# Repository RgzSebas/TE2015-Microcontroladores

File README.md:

# **TE2015 Microcontroladores**

This repository aims to help you understand the topics covered in TE2015 Microcontroladores. Particulary, we will address the following:
* To understand the architecture of a PIC18 microcontroller
* To become familiar with PIC18 instruction set to develop firmware
* To carry out coding, programming and debugging of PIC18 firmware using MPLAB X IDE
* To interface a microcontroller with an external memory or peripheral using both, physical connections and driver develpment 
* To analyze the internal structure of a general purpose input/output port of the microcontroller
* To learn by doing on the develpment of timing-based firmware 
* To study serial communication protocols to communicate a microcontroller with an external device

## Laboratory
| WEEK | DATE | LABORATORY |
| :---: | :--- | :--- |
| 32 |  8 Aug | [LB1 Hardware design: schematic capture](laboratory/LB1/README.md) |
| 33, 34 | 15, 22 Aug | [LB2 Hardware design: physicial layout](laboratory/LB2/README.md) |
| 35 | 29 Aug | [LB3 PIC18 and MPLAB basics](laboratory/LB3/README.md) |
| 36, 37 | 5, 12/Sep  | [LB4 Assembly programming of PIC18](laboratory/LB4/README.md)|
| 38, 39 | 19, 26/Sep | [LB5 Fundamentals of C for PIC programming](laboratory/LB5/README.md) |

<!--
| 41 | 3/Oct  | LB6 GPIO: LCD display |
| 42 | 10/Oct | LB7 GPIO: 4x4 keypad and 7-segment display |
| 43 | 17/Oct | LB8 Hardware interrupts and the Interrupt Service Rutines|
| 44 | 24/Oct | LB8 Hardware interrupts and the Interrupt Service Rutines|
| 45 | 31/Oct | LB9 Timers, comparators and PWM|
| 46 | 7/Nov  | LB10 Analog inputs for microcontrollers|
| 47 | 14/Nov | LB11 Asynchronous serial communications|
| 48 | 21/Nov | HOLIDAY |
-->

## Hands-on Exercises
| NAME | WEEK | TOPIC | DESCRIPTION | LANGUAGE | 
|---|---|---|---|---| 
| [PIC18F4550_BSF.X](mplab/PIC18F4550_BSF.X) | 34 | SFRs | Bank operations using BSR | PIC-AS |
<!--
| [PIC18F57Q43_GPIO_config]| 34 | SFRs & GPIO | Configuration of TRIS y ANSEL SFRs to blink an on-board LED | PIC-AS |
| XXXX | 35 | Stack & Addressing | PENDING | PIC-AS |
| XXXX | 36 | PIC18 ISA | PENDING | PIC-AS |
| XXXX | 37 | Flow control | PENDING | PIC-AS |
| XXXX | 39 | Operators and precedence | PENDING | PIC-AS |
| XXXX | 40 | Flow control | PENDING | C |
| XXXX | 41 | Pointers, Arrays & Scopes| PENDING | C |
| XXXX | 42 | GPIO | PENDING | C |
| XXXX | 44 | Interrupts | PENDING | C |
| XXXX | 45 | Timers | PENDING | C |
| XXXX | 46 | ADC & UART | PENDING | C |
-->

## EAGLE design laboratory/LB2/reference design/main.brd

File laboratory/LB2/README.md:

# LB2. Expansion Board: Physical Layout

## Description
This is the second part of the Expansion Board design. In this part you will finish designing your board by putting all the components' footprints in place inside the board and routing all of the electrical connections along the two sides of the board: top and bottom. Once you are done routing your board, it is important to carry out a test that will let you know if the component placemente and the copper tracks can be fabricated by the manufacturer, which is called the Design Rule Check (DRC). For this, we need to set the manufacturer's design rules first and then perform the test considering such rules you previously established. Once the test is passed, you can be sure the manufacturer is able to fabricate your board without setback. For a better undestanding of the PCB fabrication process, watch the video <a href="https://www.youtube.com/watch?v=YJr-kHy6STg">What is a PCB?</a>.

## Lab Procedure
### __STEP 1. SET THE DESIGN RULES__
After finishing your schematic diagram, the layout view of your board can be created. For this, go to _File_ menu and select _Switch to board_.

Once the board view is open, select _DRC_ under _Tools_ menu to open the design rule window. Across the different tabs of this windows you define the design rules of your design, according to the manufacturer fabrication capabilities. Go through tabs _Clearance_, _Distance_, _Sizes_ and _Annular Ring_ and set the parameters as shown in the figures below. Note that all distances are expressed in __mil__ units, which represents the thousandth of an inch. 

### __STEP 2. PLACE THE COMPONENTS INSIDE THE BOARD BOUNDERIES__
The figure below shows the layout view of your board including all the components and a predefined board with and area of 160 mm x 100 mm. This predifined board is enough to place and route all your components, thus you can start placing the components inside. 

Once you are done placing the components, the board should like as the one shown below. You can readjust the board dimensions if you consider more or less space is suitable for your component arrangement. 

### __STEP 3. ROUTE ALL THE CONNECTIONS__
Route your components by using the Autoroute tool. This way, the tool will make sure that design rules are fulfilled as routing takes place. The routing process will take some time, depending on your computer. To use the Autorouter tool, select _Autorouter_ under _Tools_ menu. 

You can use the predefined settings as shown below and click _Continue_. The following window shows the percentage of tracks that have been routed by the Autorouter. After clicking _Start_, the tool starts the routing process and you can monitor the progress on the same window.

Once the Autorouter has router 100% of the tracks, you can stop the process by clicking _End Job_. If you leave the process longer, it will try to optimize the tracks by reducing the track length the amount of vias that are placed. It is recommended to allow the Autorouter to optimize the design so it is less prone to fabrication errors. The figure below shows when 100% of the tracks have been routed and you can end the process.

The resulting board will show now all the tracks that interconnect the components in your board. Red tracks correspond to tracks on the top copper layer, and blue tracks show those on the bottom copper layer. 

### __STEP 4. CARRY OUT A DESIGN RULE CHECK__
Open the DRC window and click _Check_ to run the test. In case design errors are found, an error window will pop-up describing the errors found. If no errors are detected, anything will pop up and the test is passed.

### __STEP 5. GENERATE THE GERBER FILES__
Under _File_ select _CAM Processor_. On the CAM Processor window, select _Gerber_ on _Output Files_ to see the Gerber file options. The image below shows the settings for the Gerber files. Make sure `Export as ZIP` and `Gerber RS-274X` are selected.

Under the _Gerber_ tab you can see all the different layers on you design, such as top and bottom copper, soldermasks, silkscreens, etc. Clicking on any of the layers will shown a preview of such layer. 

To generate your files click _Process Job_, find a location for your ZIP file and click _Save_.

The files will be then generated and located in the folder of your choice. 

### __STEP 6. SEND OUT YOUR FILES FOR BOARD MANUFACTURE__
Some manufacturers have a quotation system that allow you to upload your GERBER files to then generate an estimated price for your design. Select the minimum quantity of boards that the manufacturer can fabricate and get an approximate cost for your design. See below three reliable manufacturers with an self quotation system that you can use for your  board:

<p align="center">

</p>

### __STEP 7. GET THE ELECTRONIC COMPONENTS__
The final step is to get the electronic components for your board. In this sense, there is a pre-made Bill of Materials (BOM) that keeps an updated list of components required for the assembly. It is kept on Digikey and you can access it following the link below:
<p align="center">
</p>

The BOM keeps the minimum amount of each component required to assembly one board. Feel free to modify the component quantity in case you want to assemble more than one board or get spares in case you loose or damage any component during assembly and soldering.

If you would like to receive your components at campus instead of a personal address, ask your professor for address details. 

### __DELIVERABLES__
Deliverables for LB2 are:
1. EAGLE project 
   * Include the schematic diagram without ERC errors.
   * PCB layout without DRC errors  
   * Push your project files into your GitHub repository.
2. Demostrative video 
   * Make a 2-minutes video showing the finished board to complement your last video presentation. In this case, perform a DRC test to demonstrate that your design is ready for fabrication.
   * Also, explain the process to generate the Gerber files and show the quotation you get from the manufacturer of your choice.
      
      _Note that a similar DRC will be carried out by the manufacturer to make sure your board can be manufactured. You will get a confirmation if your design is ready for fabrication_. 
   * _Optional:_ Show the 3D view of your video on Fusion 360.

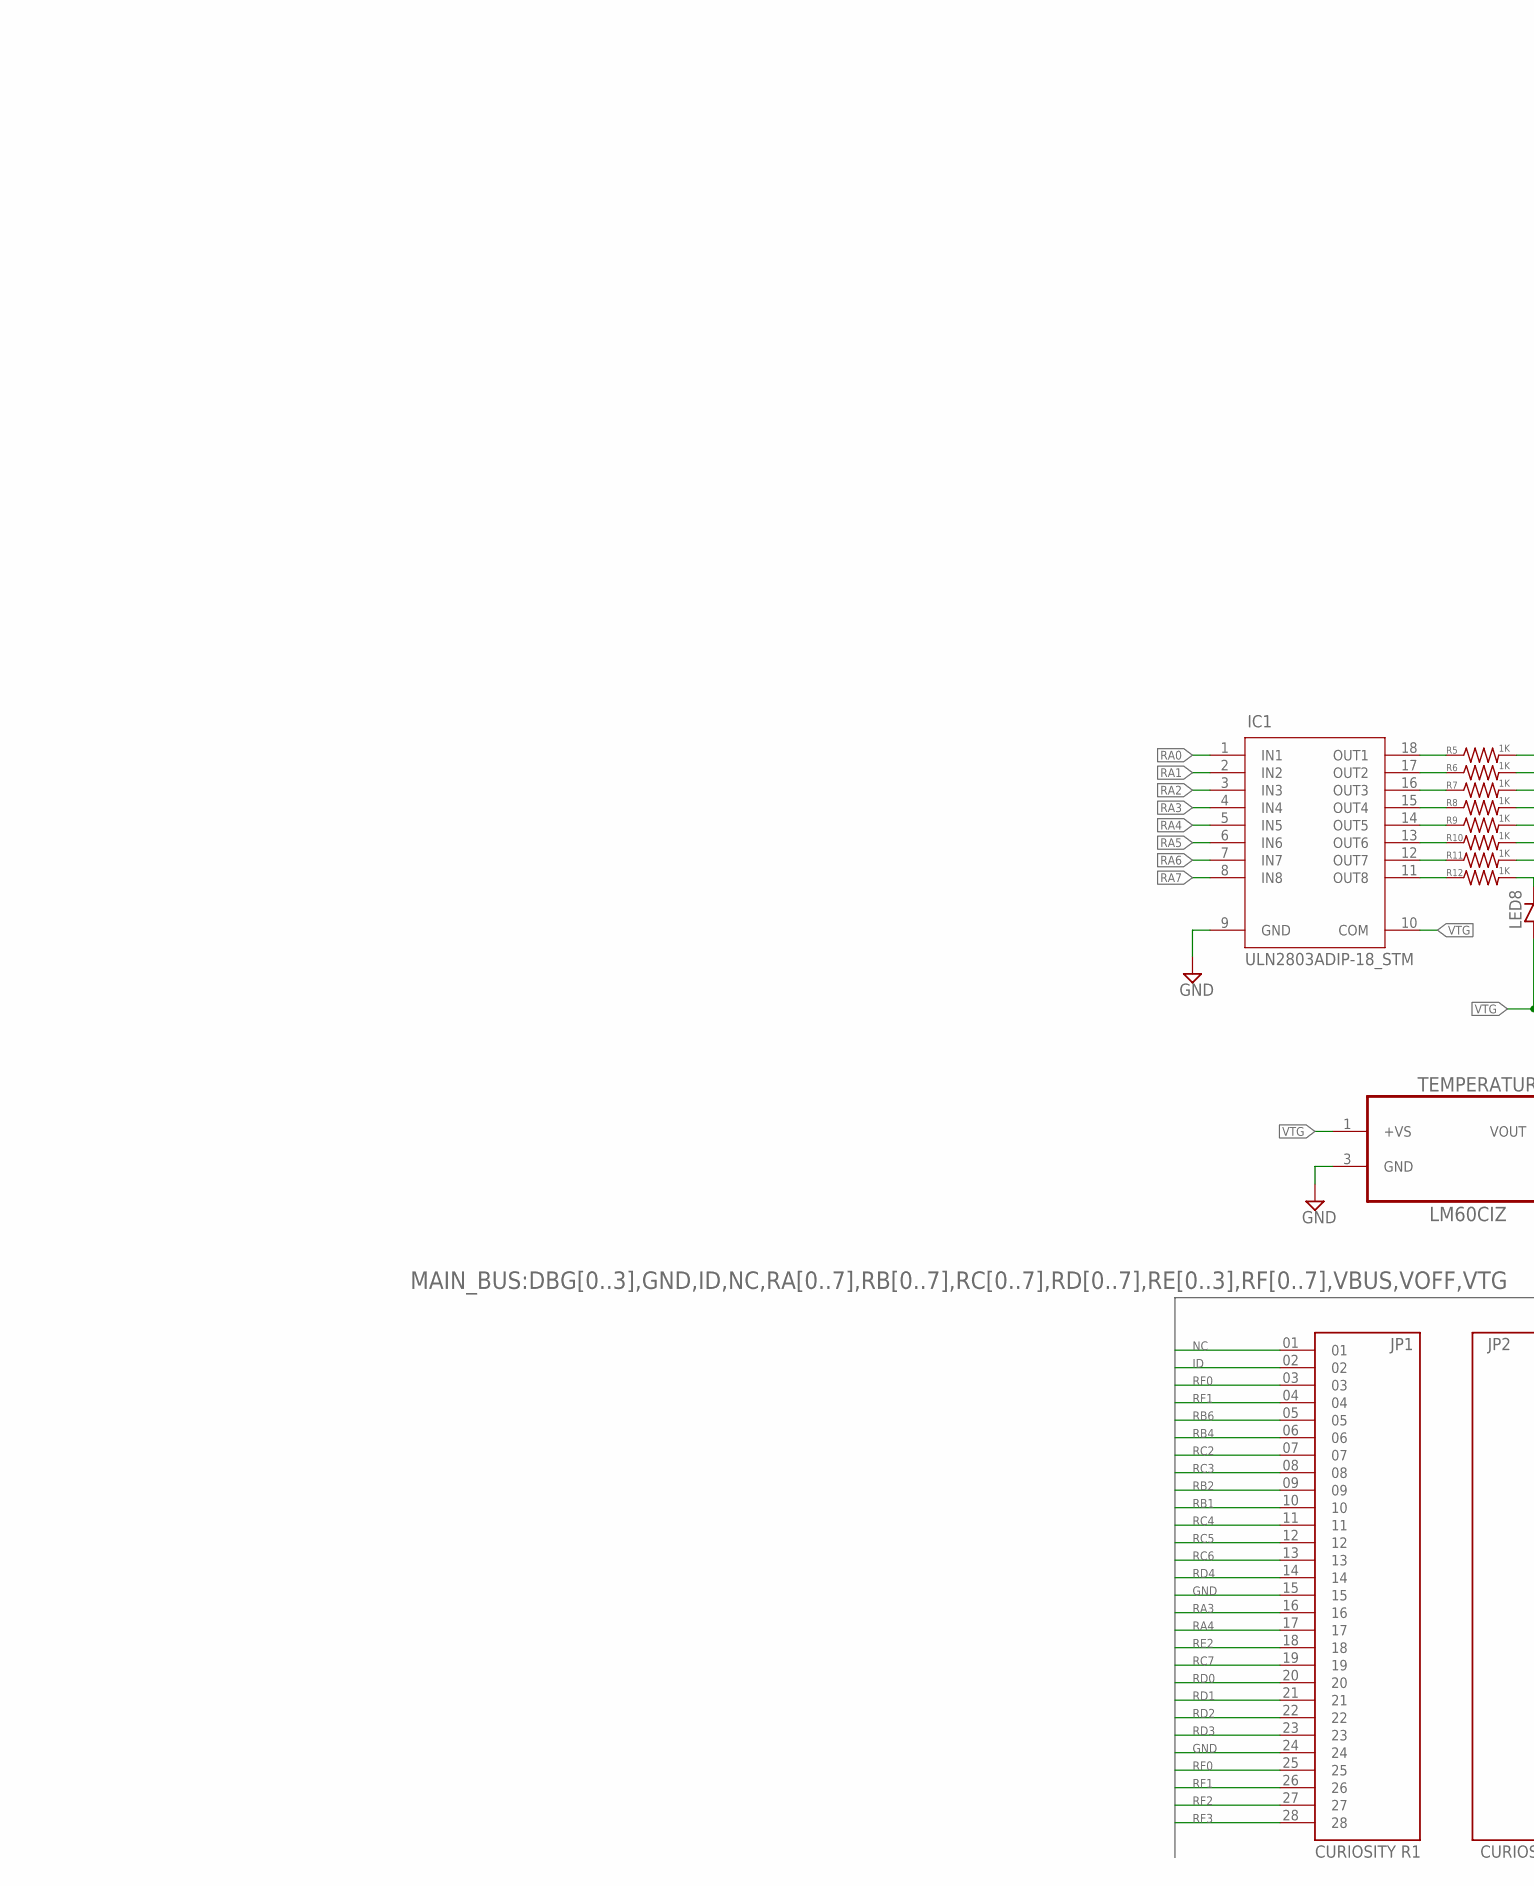
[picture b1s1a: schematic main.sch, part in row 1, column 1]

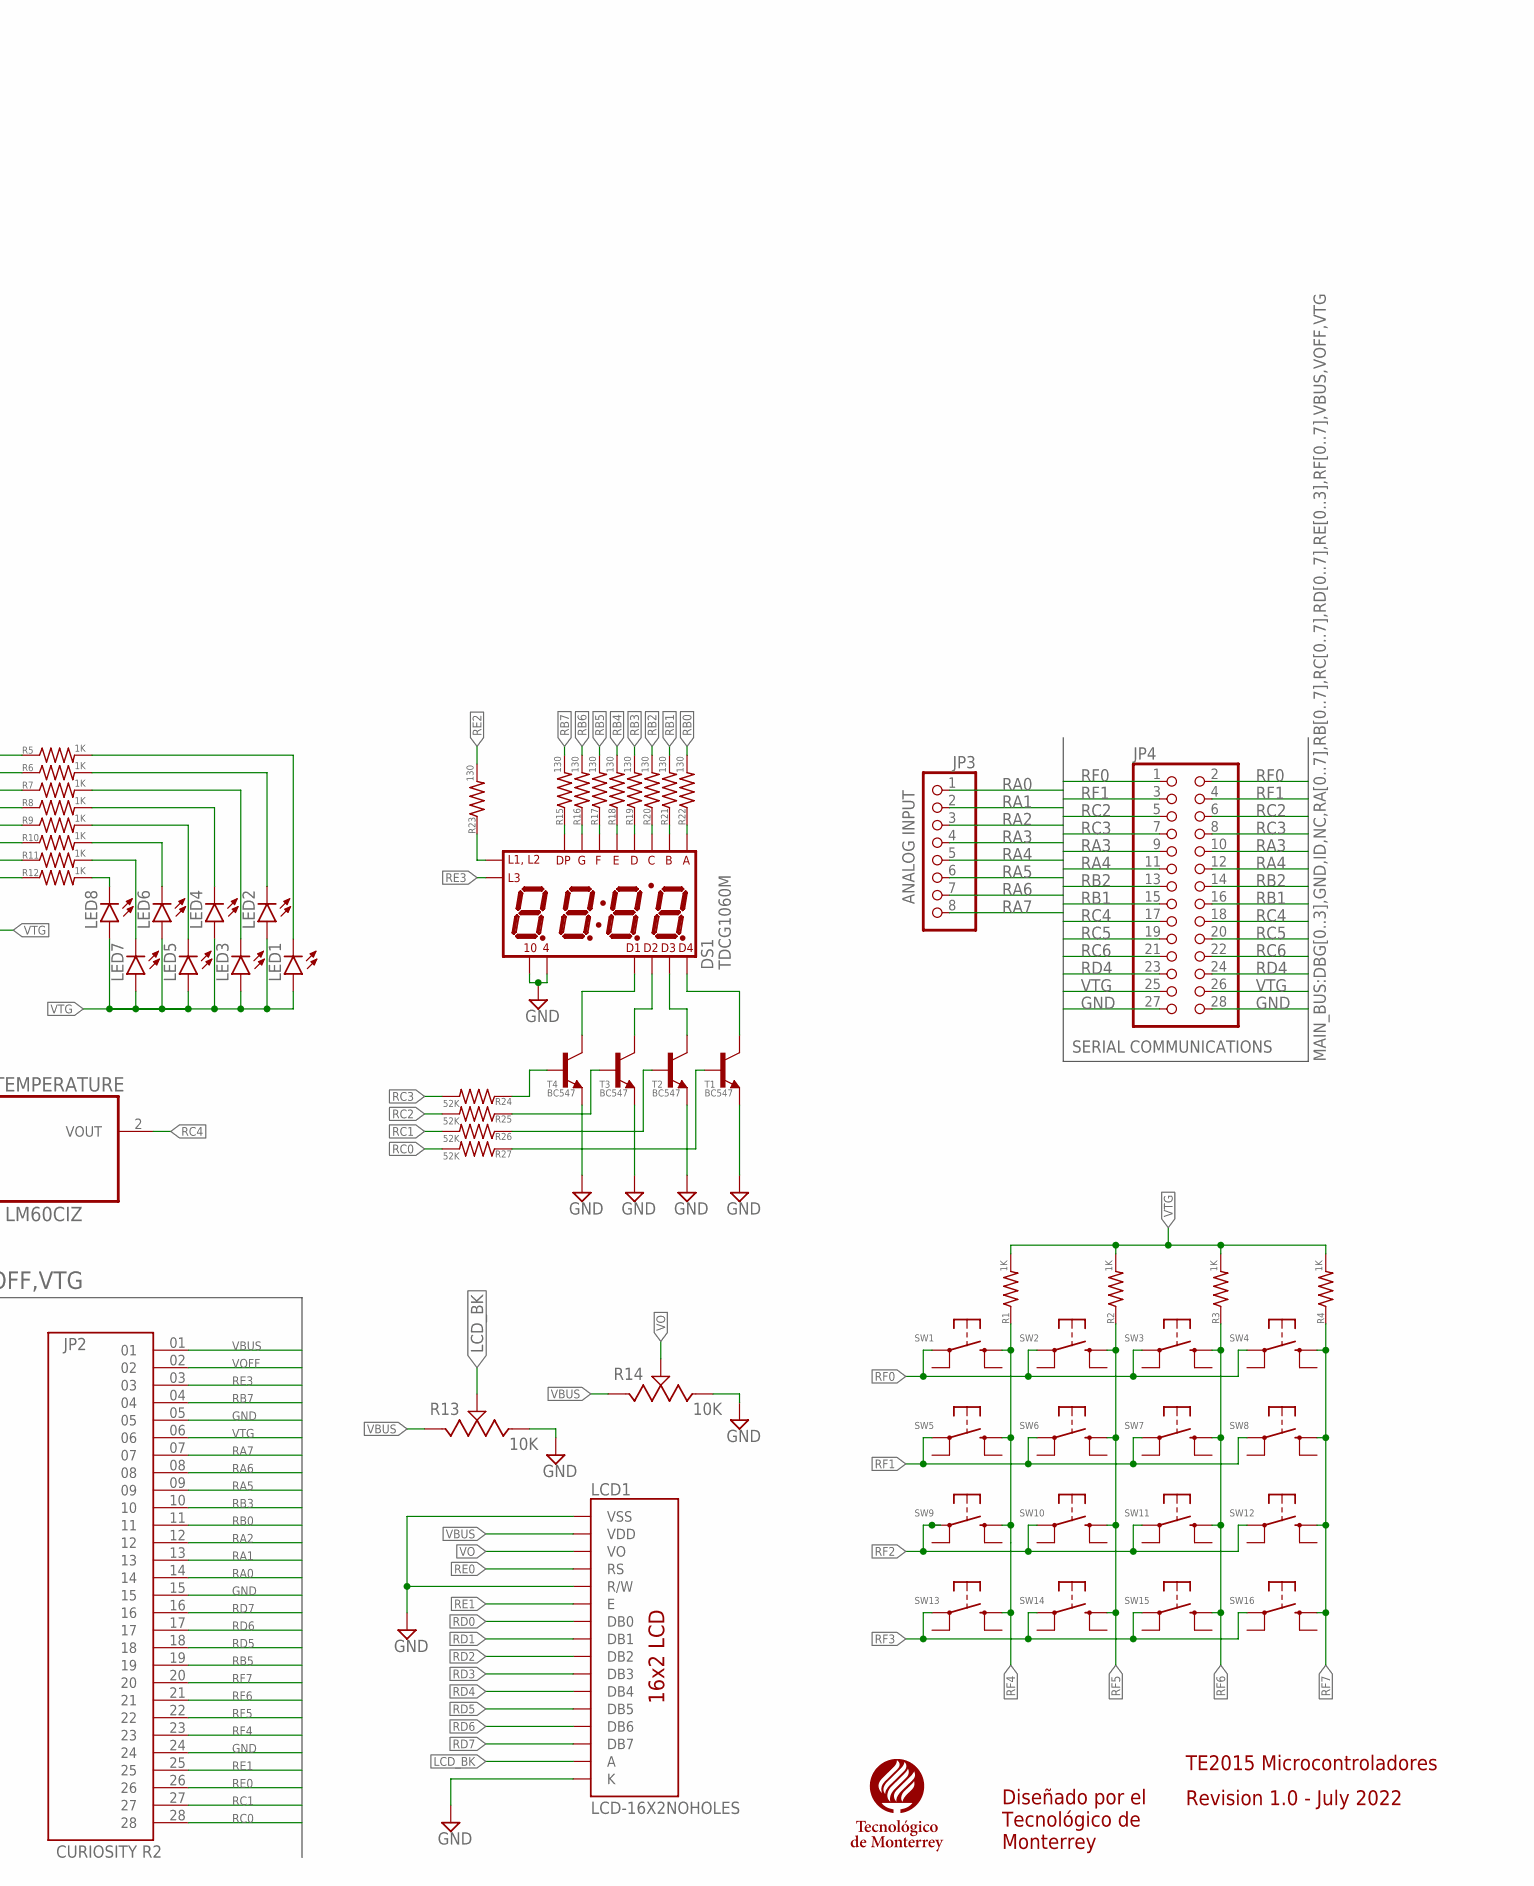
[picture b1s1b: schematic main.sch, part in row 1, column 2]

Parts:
DS1: TDCG1060M; DISPLAY_TDCG1060M
IC1: ULN2803ADIP-18_STM; DIP-18_STM
JP1: CURIOSITY R1; SAMTEC_SS-128-T-2
JP2: CURIOSITY R2; SAMTEC_SS-128-T-2
JP3: ANALOG INPUT; 1X08-BIG
JP4: SERIAL COMMUNICATIONS; 2X14-BIG
LCD1: LCD-16X2NOHOLES; LCD-16X2_NOHOLESNOSILK
LED1, LED2, LED3, LED4, LED5, LED6, LED7, LED8: LED3MM
R1, R2, R3, R4, R5, R6, R7, R8, R9, R10, R11, R12: 1K; 0207/10
R13, R14: 10K; 3362P-1-103LF
R15, R16, R17, R18, R19, R20, R21, R22, R23: 130; 0207/10
R24, R25, R26, R27: 52K; 0207/10
SW1, SW2, SW3, SW4, SW5, SW6, SW7, SW8, SW9, SW10, SW11, SW12, SW13, SW14, SW15, SW16: 1825910-2; TE_1825910-2
T1, T2, T3, T4: BC547; TO92
TEC1: TEC_LOGO
TEMPERATURE: LM60CIZ; TO92/

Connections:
GND: DS1.4, DS1.10, IC1.9 (GND), JP1.15, JP1.24, JP2.05, JP2.15, JP2.24, JP4.27, JP4.28, LCD1.1 (VSS), LCD1.5 (R/W), LCD1.16 (K), R13.3, R14.3, T1.1 (E), T2.1 (E), T3.1 (E), T4.1 (E), TEMPERATURE.3 (GND)
ID: JP1.02
LCD_BK: LCD1.15 (A), R13.2
unnamed: IC1.18 (OUT1), R5.1
unnamed: LED8.K (C), R12.2
unnamed: LED7.K (C), R11.2
unnamed: LED6.K (C), R10.2
unnamed: LED5.K (C), R9.2
unnamed: LED4.K (C), R8.2
unnamed: LED3.K (C), R7.2
unnamed: LED2.K (C), R6.2
unnamed: DS1.7 (DP), R15.1
unnamed: DS1.15 (G), R16.1
unnamed: DS1.11 (F), R17.1
unnamed: DS1.5 (E), R18.1
unnamed: DS1.3 (D), R19.1
unnamed: DS1.13 (C), R20.1
unnamed: DS1.16 (B), R21.1
unnamed: DS1.14 (A), R22.1
unnamed: IC1.17 (OUT2), R6.1
unnamed: IC1.16 (OUT3), R7.1
unnamed: LED1.K (C), R5.2
unnamed: IC1.15 (OUT4), R8.1
unnamed: DS1.12 (L1_L2), R23.1
unnamed: IC1.14 (OUT5), R9.1
unnamed: IC1.13 (OUT6), R10.1
unnamed: IC1.12 (OUT7), R11.1
unnamed: IC1.11 (OUT8), R12.1
unnamed: DS1.1 (DIG1), T4.3 (C)
unnamed: R24.1, T4.2 (B)
unnamed: DS1.8 (DIG4), T1.3 (C)
unnamed: DS1.6 (DIG3), T2.3 (C)
unnamed: DS1.2 (DIG2), T3.3 (C)
unnamed: R25.1, T3.2 (B)
unnamed: R26.1, T2.2 (B)
unnamed: R27.1, T1.2 (B)
NC: JP1.01
RA0: IC1.1 (IN1), JP2.14, JP3.1
RA1: IC1.2 (IN2), JP2.13, JP3.2
RA2: IC1.3 (IN3), JP2.12, JP3.3
RA3: IC1.4 (IN4), JP1.16, JP3.4, JP4.9, JP4.10
RA4: IC1.5 (IN5), JP1.17, JP3.5, JP4.11, JP4.12
RA5: IC1.6 (IN6), JP2.09, JP3.6
RA6: IC1.7 (IN7), JP2.08, JP3.7
RA7: IC1.8 (IN8), JP2.07, JP3.8
RB0: JP2.11, R22.2
RB1: JP1.10, JP4.15, JP4.16, R21.2
RB2: JP1.09, JP4.13, JP4.14, R20.2
RB3: JP2.10, R19.2
RB4: JP1.06, R18.2
RB5: JP2.19, R17.2
RB6: JP1.05, R16.2
RB7: JP2.04, R15.2
RC0: JP2.28, R27.2
RC1: JP2.27, R26.2
RC2: JP1.07, JP4.5, JP4.6, R25.2
RC3: JP1.08, JP4.7, JP4.8, R24.2
RC4: JP1.11, JP4.17, JP4.18, TEMPERATURE.2 (VOUT)
RC5: JP1.12, JP4.19, JP4.20
RC6: JP1.13, JP4.21, JP4.22
RC7: JP1.19
RD0: JP1.20, LCD1.7 (DB0)
RD1: JP1.21, LCD1.8 (DB1)
RD2: JP1.22, LCD1.9 (DB2)
RD3: JP1.23, LCD1.10 (DB3)
RD4: JP1.14, JP4.23, JP4.24, LCD1.11 (DB4)
RD5: JP2.18, LCD1.12 (DB5)
RD6: JP2.17, LCD1.13 (DB6)
RD7: JP2.16, LCD1.14 (DB7)
RE0: JP2.26, LCD1.4 (RS)
RE1: JP2.25, LCD1.6 (E)
RE2: JP1.18, R23.2
RE3: DS1.9 (L3), JP2.03
RF0: JP1.03, JP1.25, JP4.1, JP4.2, SW1.1, SW2.1, SW3.1, SW4.1
RF1: JP1.04, JP1.26, JP4.3, JP4.4, SW5.1, SW6.1, SW7.1, SW8.1
RF2: JP1.27, SW9.1, SW10.1, SW11.1, SW12.1
RF3: JP1.28, SW13.1, SW14.1, SW15.1, SW16.1
RF4: JP2.23, R1.1, SW1.2 (S), SW5.2 (S), SW9.2 (S), SW13.2 (S)
RF5: JP2.22, R2.1, SW2.2 (S), SW6.2 (S), SW10.2 (S), SW14.2 (S)
RF6: JP2.21, R3.1, SW3.2 (S), SW7.2 (S), SW11.2 (S), SW15.2 (S)
RF7: JP2.20, R4.1, SW4.2 (S), SW8.2 (S), SW12.2 (S), SW16.2 (S)
VBUS: JP2.01, LCD1.2 (VDD), R13.1, R14.1
VO: LCD1.3 (VO), R14.2
VOFF: JP2.02
VTG: IC1.10 (COM), JP2.06, JP4.25, JP4.26, LED1.A, LED2.A, LED3.A, LED4.A, LED5.A, LED6.A, LED7.A, LED8.A, R1.2, R2.2, R3.2, R4.2, TEMPERATURE.1 (+VS)

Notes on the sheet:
TE2015 Microcontroladores
Revision 1.0 - July 2022
Diseñado por el Tecnológico de Monterrey

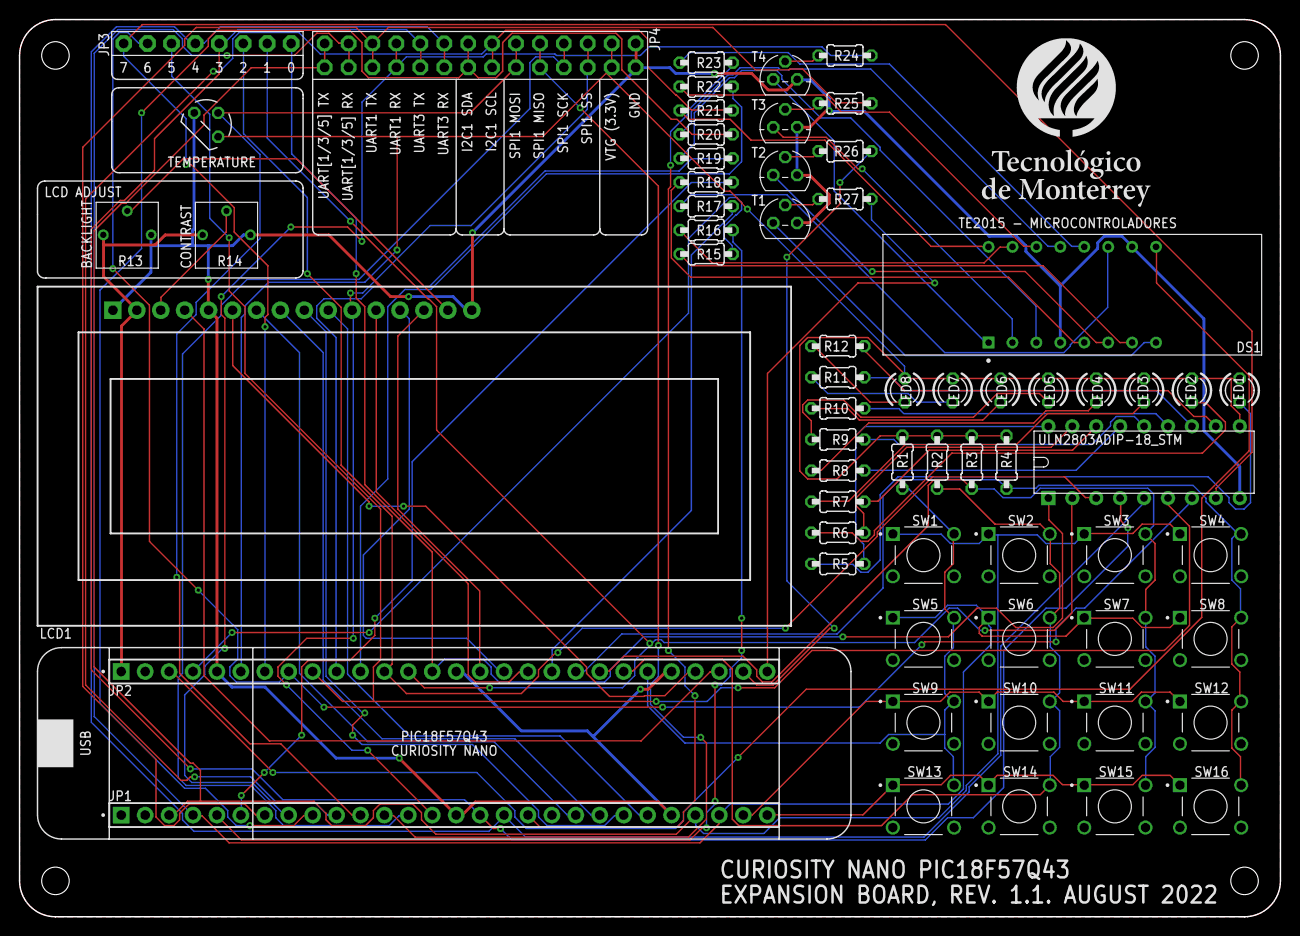
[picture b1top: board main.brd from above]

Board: 2 copper layers, 133.9 x 95.2 mm, 64 parts (0 on the bottom side), 81 nets.

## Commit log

2022-08-04 LB1 COMPLETED
2022-08-04 Corrected circuit table format
2022-08-08 Changed deliverables for LB1!
2022-08-08 Added Datasheet folder
2022-08-15 LB2 initial commit
2022-08-17 Eagle reference design added
2022-08-17 Deleted redundant files from reference design
2022-08-19 Steps 6 and 7 completed
2022-08-19 Link to LB2
2022-08-19 BSR example updated for class
2022-08-19 Deleted redundant files
2022-08-19 Link to BSF example
2022-08-28 Initial commit of LB3
2022-08-28 Instructions for xercises 1 and 2, and Deliverables completed
2022-08-28 LB3 link added to frontpage
2022-08-28 LB3 title corrected from LB2 to LB3
2022-08-28 corrected title to LB3. Objectives specified. Removed innecessary paragraphs from PRE-LAB work.
2022-08-28 Corrected LB3 title
2022-09-01 Course file tree organized
2022-09-01 removed duplicated folder
2022-09-02 Added PIC-AS MPLAB X project template
2022-09-02 corrected instruction 1
2022-09-02 added code to enable RB4 as input for exercise 10
2022-09-02 added PORT A configuration
2022-09-04 added extracted sections from PIC18F57Q43 datasheet
2022-09-04 added BlinkLED_PIC18F45K50.hex
2022-09-05 LB4 isntructions completed, review pending
2022-09-05 corrected LB4 objectives
2022-09-05 added configuration_bits.inc and delays.inc
2022-09-05 added reference code to Exercise 2
2022-09-09 updated HW2 MPLAB project with solved exercises
2022-09-18 LB5 instructions v1.0 done
2022-09-18 LB5 v1.0
2022-09-18 LB5 description added
2022-09-19 added LB5 link on front page
2022-09-19 LB5 files cleaned up
2022-09-26 LB6 instructions
2022-09-26 resized pullups3.png
2022-09-26 corrected numbering
2022-09-29 add knight_rider.c, mustang.c and MCC scripts
2022-09-29 update mustang.c comments

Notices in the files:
parts and their libraries:
COPYRIGHT: Copyright (C) 2022 Ultra Librarian. All rights reserved.
